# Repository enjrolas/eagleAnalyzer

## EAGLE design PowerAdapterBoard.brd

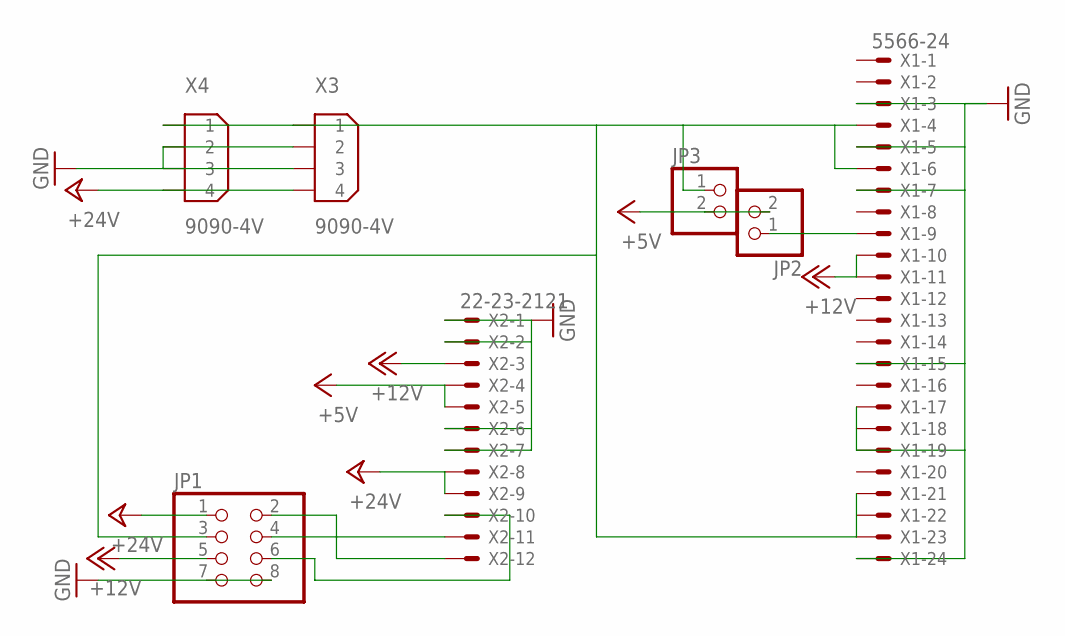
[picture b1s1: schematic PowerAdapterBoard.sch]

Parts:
JP1: PINHD-2X4; 2X04
JP2, JP3: PINHD-1X2; 1X02
X1: 5566-24
X2: 22-23-2121
X3, X4: 9090-4V

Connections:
+5V: JP2.2, JP3.2, X2.4, X2.5
+12V: JP1.5, X1.10, X1.11, X2.3
+24V: JP1.1, X2.8, X2.9, X3.4, X4.4
GND: JP1.7, JP1.8, X1.3, X1.5, X1.7, X1.15, X1.17, X1.18, X1.19, X1.24, X2.1, X2.2, X2.6, X2.7, X3.2, X3.3, X4.2, X4.3
unnamed: JP1.6, X2.10
unnamed: JP1.4, X2.11
unnamed: JP1.2, X2.12
unnamed: JP2.1, X1.9
unnamed: JP1.3, JP3.1, X1.4, X1.6, X1.21, X1.22, X1.23, X3.1, X4.1

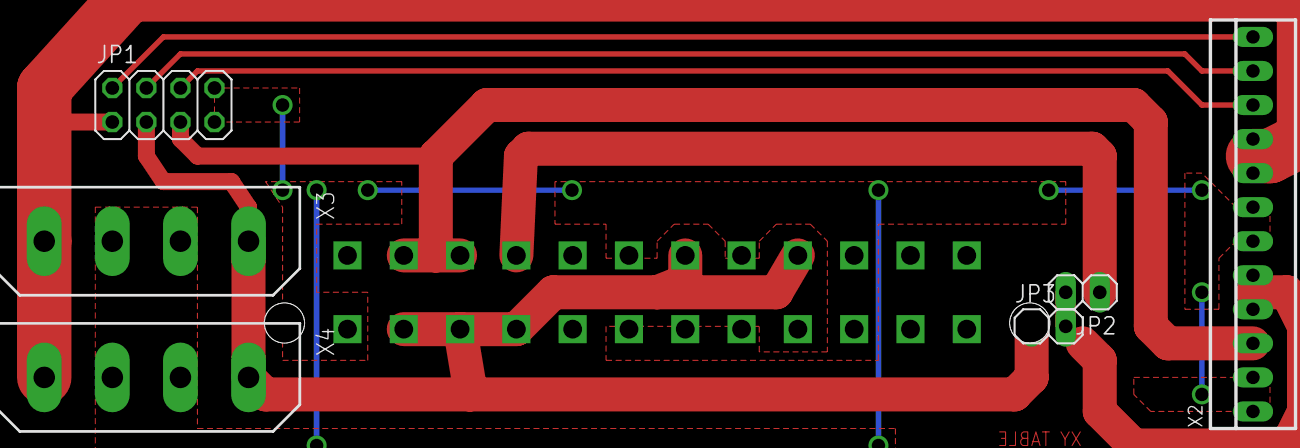
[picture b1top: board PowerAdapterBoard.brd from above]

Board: 2 copper layers, 7 parts (1 on the bottom side), 9 nets.

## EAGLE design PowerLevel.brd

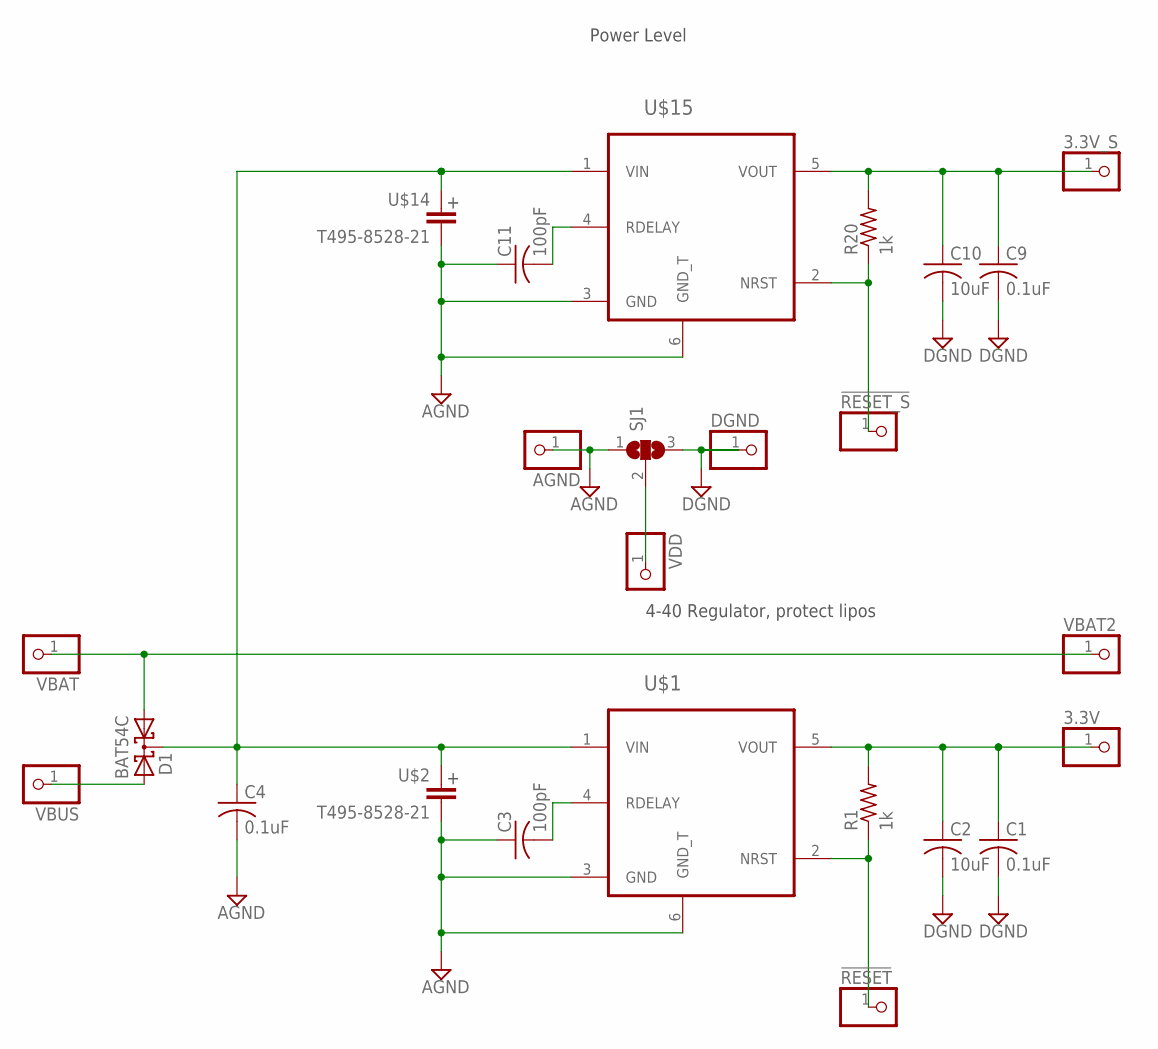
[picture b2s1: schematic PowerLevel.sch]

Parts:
3.3V, 3.3V_S: PINHD-1X1; 1X01
!RESET: PINHD-1X1; 1X01
!RESET_S: PINHD-1X1; 1X01
AGND: PINHD-1X1; 1X01
C1, C9: 0.1uF; C0402
C2, C10: 10uF; C0402
C3, C11: 100pF; C0402K
C4: 0.1uF; C0402K
D1: BAT54C; SOT23
DGND: PINHD-1X1; 1X01
R1, R20: 1k; R0402
SJ1: SJ2WW; SJ_2W
U$1, U$15: TPS7A6033-Q1; TO-263-5
U$2, U$14: T495-8528-21; 8528-21
VBAT, VBAT2: PINHD-1X1; 1X01
VBUS: PINHD-1X1; 1X01
VDD: PINHD-1X1; 1X01

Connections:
3.3V_SECONDARY: 3.3V_S.1, C9.1, C10.1, R20.2, U$15.5 (VOUT)
AGND: AGND.1, C3.1, C4.2, C11.1, SJ1.1, U$1.3 (GND), U$1.6 (GND_T), U$2.NEG (2), U$14.NEG (2), U$15.3 (GND), U$15.6 (GND_T)
DGND: C1.2, C2.2, C9.2, C10.2, DGND.1, SJ1.3
unnamed: 3.3V.1, C1.1, C2.1, R1.2, U$1.5 (VOUT)
unnamed: C4.1, D1.3 (CC), U$1.1 (VIN), U$2.POS (1), U$14.POS (1), U$15.1 (VIN)
unnamed: SJ1.2, VDD.1
unnamed: C3.2, U$1.4 (RDELAY)
unnamed: C11.2, U$15.4 (RDELAY)
unnamed: !RESET.1, R1.1, U$1.2 (NRST)
unnamed: !RESET_S.1, R20.1, U$15.2 (NRST)
VBAT: D1.1 (A1), VBAT.1, VBAT2.1
VUSB: D1.2 (A2), VBUS.1

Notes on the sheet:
4-40 Regulator, protect lipos
Power Level

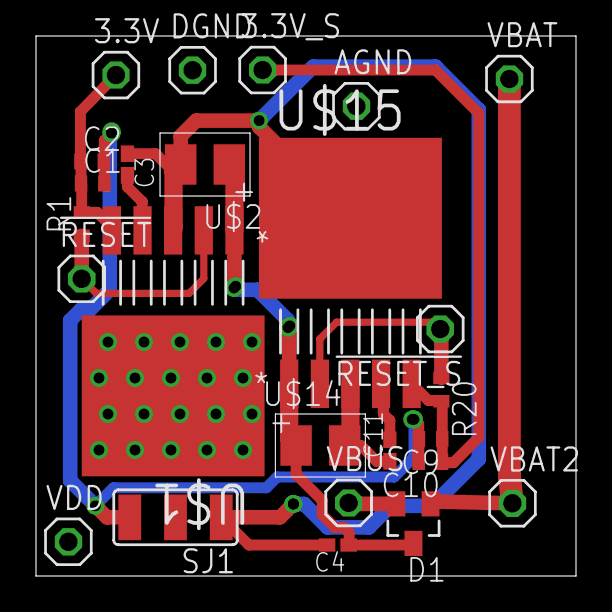
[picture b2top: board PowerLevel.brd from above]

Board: 2 copper layers, 30.0 x 30.0 mm, 25 parts (0 on the bottom side), 12 nets.

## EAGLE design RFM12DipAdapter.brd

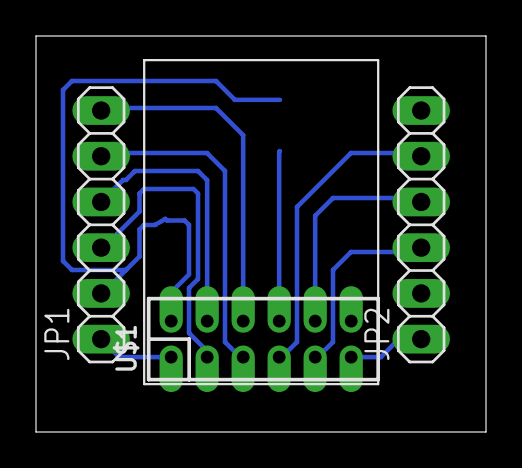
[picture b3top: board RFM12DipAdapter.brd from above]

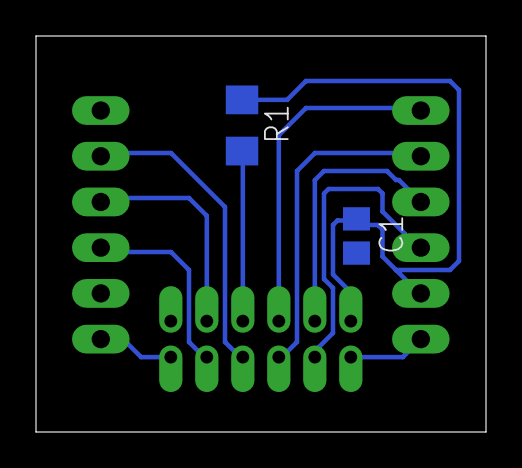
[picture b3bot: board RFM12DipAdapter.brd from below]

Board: 2 copper layers, 25.0 x 22.0 mm, 5 parts (2 on the bottom side), 12 nets.

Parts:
C1: C0805
JP1, JP2: 1X06
R1: R1206
U$1: RFM12_DIP; DIL-2MM-2X06

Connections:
CLK: JP2.4, U$1.10
DCLK: JP2.3, U$1.9
GND: C1.2, JP2.2, U$1.12
INT: JP1.1, U$1.1
IRQ: JP2.5, U$1.7
unnamed: R1.2, U$1.8
RES: JP2.1, U$1.11
SCK: JP1.4, U$1.4
SDI: JP1.3, U$1.3
SDO: JP1.6, U$1.6
SEL: JP1.5, U$1.5
VCC: C1.1, JP1.2, R1.1, U$1.2

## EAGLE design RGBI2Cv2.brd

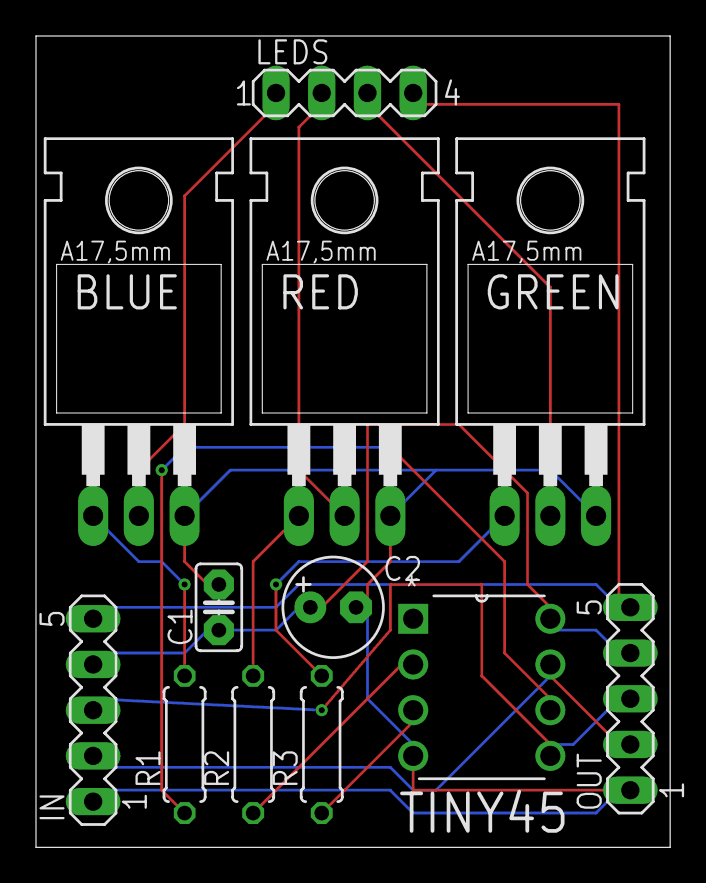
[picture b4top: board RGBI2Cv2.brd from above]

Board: 2 copper layers, 35.2 x 45.1 mm, 12 parts (0 on the bottom side), 14 nets.

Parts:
BLUE: STP16NF06; TO220BH
C1: 0.1uF; C025-025X050
C2: 100/6VuF; E2,5-6
GREEN: STP16NF06; TO220BH
IN: MA05-1
LEDS: MA04-1
OUT: MA05-1
R1, R2, R3: 10K; 0207/7
RED: STP16NF06; TO220BH
TINY45: ATTINY45-20PU; DIP254P762X533-8

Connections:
12V: IN.5, LEDS.4, OUT.5
GND: BLUE.S, C1.2, C2.-, GREEN.S, IN.1, OUT.1, RED.S, TINY45.4
unnamed: BLUE.D, LEDS.1
unnamed: LEDS.2, RED.D
unnamed: IN.2, OUT.2, TINY45.7
unnamed: IN.3, OUT.3, TINY45.5
unnamed: R1.1, TINY45.6
unnamed: BLUE.G, R1.2
unnamed: R2.2, RED.G
unnamed: GREEN.G, R3.2
unnamed: R2.1, TINY45.2
unnamed: R3.1, TINY45.3
unnamed: GREEN.D, LEDS.3
VCC5V: C1.1, C2.+, IN.4, OUT.4, TINY45.8

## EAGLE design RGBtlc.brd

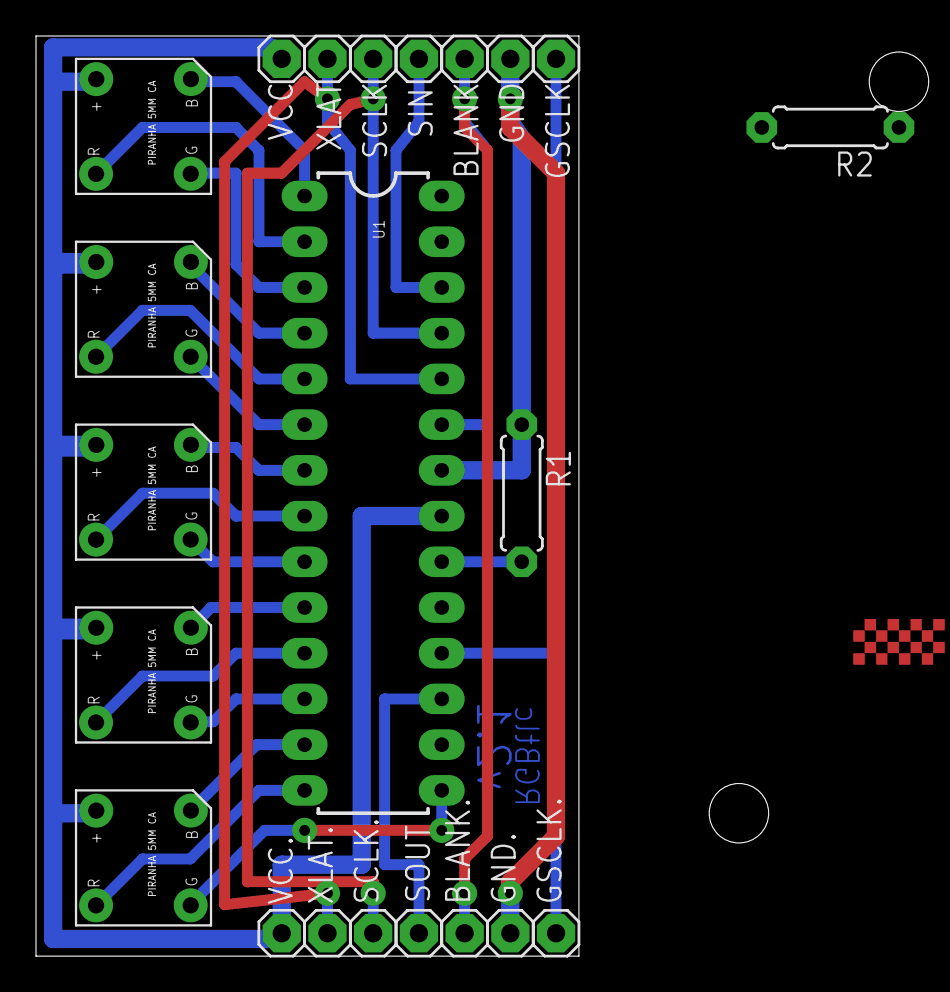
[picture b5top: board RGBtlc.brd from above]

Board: 2 copper layers, 30.2 x 51.1 mm, 24 parts (0 on the bottom side), 24 nets.

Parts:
BLANK, BLANK.: 1X01
GND, GND.: 1X01
GSCLK, GSCLK.: 1X01
JP1, JP4: STAND-OFF
R1: 2k2; 0207/7
R2: 10k; 0207/7
SCLK, SCLK.: 1X01
SIN: 1X01
SOUT: 1X01
U1: TLC5940-NT; DIL28-3
U$1, U$2, U$3, U$4, U$5: LED_PIRANHA_5MM
VCC, VCC.: 1X01
XLAT, XLAT.: 1X01

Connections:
GND: GND.1, GND..1, R1.1, U1.22
unnamed: U1.15, U$5.G
unnamed: U1.14, U$5.R
unnamed: U1.13, U$5.B
unnamed: U1.7, U$3.B
unnamed: U1.12, U$4.G
unnamed: U1.11, U$4.R
unnamed: U1.10, U$4.B
unnamed: U1.9, U$3.G
unnamed: BLANK.1, BLANK..1, U1.23
unnamed: U1.6, U$2.G
unnamed: U1.5, U$2.R
unnamed: U1.4, U$2.B
unnamed: U1.3, U$1.G
unnamed: U1.2, U$1.R
unnamed: U1.1, U$1.B
unnamed: SCLK.1, SCLK..1, U1.25
unnamed: SIN.1, U1.26
unnamed: U1.24, XLAT.1, XLAT..1
unnamed: GSCLK.1, GSCLK..1, U1.18
unnamed: SOUT.1, U1.17
unnamed: R1.2, U1.20
unnamed: U1.8, U$3.R
VCC: U1.21, U$1.+, U$2.+, U$3.+, U$4.+, U$5.+, VCC.1, VCC..1

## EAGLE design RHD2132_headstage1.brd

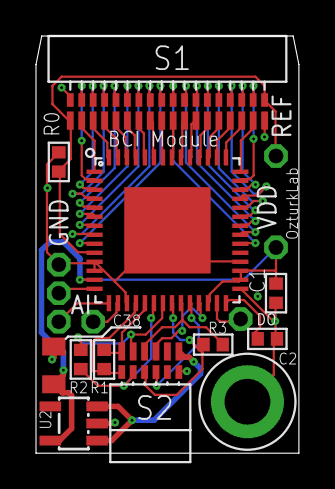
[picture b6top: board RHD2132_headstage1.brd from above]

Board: 4 copper layers, 14.6 x 23.2 mm, 19 parts (0 on the bottom side), 49 nets.

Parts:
AI: TESTPOINT_SMALL
C1: 100n; 0402
C2: 10n; 0402
C38: 10uF; R/2012-12R
DO: TESTPOINT_SMALL
GND: TESTPOINT_SMALL
H1: SCREW_HOLE_2-56
IN2, IN3: TESTPOINT_SMALL
R0: 0; 0402
R1, R2, R3: 100; 0402
REF: TESTPOINT_SMALL
S1: OMNETICS_A79025
S2: RHD2000-CABLE-AMP-SIDE; OMNETICS_PZN-12-AA
U1: RHD2132_QFN; QFN56_8_X_8_LARGE
U2: FAN2500S33X; SOT23-5$2
VDD: TESTPOINT_SMALL

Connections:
5V: S2.T6, U2.1, U2.3
GND: C1.2, C2.2, C38.-, GND.1, H1.1, R0.1, S1.B1, S1.T18, S2.B6, U1.11, U1.12, U1.17, U1.29, U1.32, U1.CENTER, U2.2
unnamed: R0.2, REF.1, S1.B18, S1.T1, U1.10
unnamed: S1.B3, U1.3
unnamed: S1.B2, U1.2
unnamed: S1.B4, U1.4
unnamed: S1.B5, U1.5
unnamed: S1.B6, U1.6
unnamed: S1.B7, U1.7
unnamed: S1.B8, U1.8
unnamed: S1.B9, U1.9
unnamed: R1.1, S2.B1, U1.18
unnamed: S1.B17, U1.41
unnamed: S1.B16, U1.40
unnamed: S1.B15, U1.39
unnamed: S1.B14, U1.38
unnamed: S1.B13, U1.37
unnamed: S1.B12, U1.36
unnamed: S1.B11, U1.35
unnamed: S1.T9, U1.50
unnamed: S1.T8, U1.51
unnamed: S1.T7, U1.52
unnamed: S1.T3, U1.56
unnamed: S1.T4, U1.55
unnamed: S1.T5, U1.54
unnamed: S1.T6, U1.53
unnamed: S1.T10, U1.49
unnamed: S1.T11, U1.48
unnamed: S1.T12, U1.47
unnamed: S1.T13, U1.46
unnamed: S1.T14, U1.45
unnamed: S1.T15, U1.44
unnamed: S1.T16, U1.43
unnamed: S1.T2, U1.1
unnamed: S1.T17, U1.42
unnamed: R1.2, S2.T1, U1.19
unnamed: R2.1, S2.B2, U1.20
unnamed: R2.2, S2.T2, U1.21
unnamed: R3.1, S2.B3, U1.22
unnamed: R3.2, S2.T3, U1.23
unnamed: S2.B4, U1.24
unnamed: S2.T4, U1.25
unnamed: C2.1, U1.28
unnamed: DO.1, U1.27
unnamed: AI.1, U1.14
unnamed: IN2.1, U1.15
unnamed: IN3.1, U1.16
unnamed: S1.B10, U1.34
VCC: C1.1, C38.+, U1.13, U1.26, U1.30, U1.31, U2.5, VDD.1

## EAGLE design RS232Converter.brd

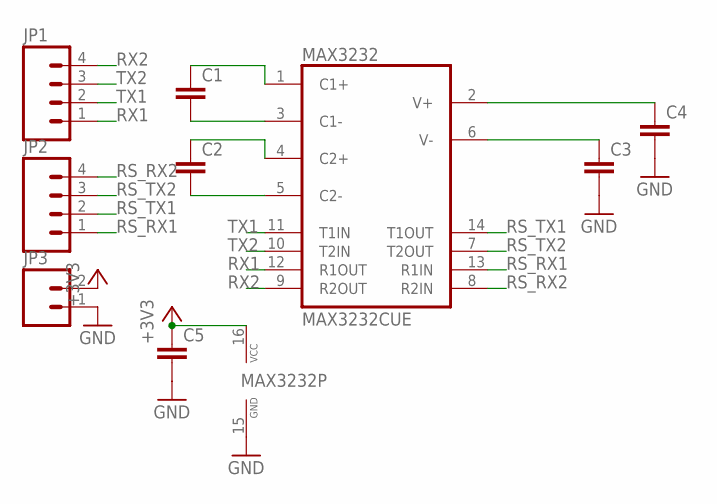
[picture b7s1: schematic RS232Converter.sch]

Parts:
C1, C2, C3, C4, C5: CAP0603-CAP; 0603-CAP
JP1, JP2: M04PTH; 1X04
JP3: M02PTH; 1X02
MAX3232: MAX3232CUE; TSSOP16

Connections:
+3V3: C5.1, JP3.2, MAX3232.16 (VCC)
GND: C3.2, C4.2, C5.2, JP3.1, MAX3232.15 (GND)
unnamed: C1.1, MAX3232.1 (C1+)
unnamed: C1.2, MAX3232.3 (C1-)
unnamed: C2.1, MAX3232.4 (C2+)
unnamed: C3.1, MAX3232.6 (V-)
unnamed: C4.1, MAX3232.2 (V+)
unnamed: C2.2, MAX3232.5 (C2-)
RS_RX1: JP2.1, MAX3232.13 (R1IN)
RS_RX2: JP2.4, MAX3232.8 (R2IN)
RS_TX1: JP2.2, MAX3232.14 (T1OUT)
RS_TX2: JP2.3, MAX3232.7 (T2OUT)
RX1: JP1.1, MAX3232.12 (R1OUT)
RX2: JP1.4, MAX3232.9 (R2OUT)
TX1: JP1.2, MAX3232.11 (T1IN)
TX2: JP1.3, MAX3232.10 (T2IN)

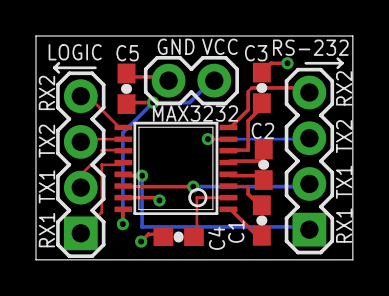
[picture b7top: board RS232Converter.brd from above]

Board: 2 copper layers, 17.6 x 12.4 mm, 9 parts (0 on the bottom side), 16 nets.

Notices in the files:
parts and their libraries:
SparkFun-DigitalIC: Licensing: CC v3.0 Share-Alike You are welcome to use this library for commercial purposes.
